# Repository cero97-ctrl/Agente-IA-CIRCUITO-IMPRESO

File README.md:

# Agente IA de Fabricación Digital.

## Estado del Proyecto
El proyecto está en desarrollo activo. Las funcionalidades principales de generación de modelos 3D y PCBs son estables. El versionado se gestiona automáticamente mediante el script `git-update.sh`.

## Descripción del Proyecto

Este repositorio aloja un **Agente de IA para Fabricación Digital**, accesible a través de un bot de Telegram. El agente está diseñado para ser un asistente de ingeniería que puede interpretar lenguaje natural e imágenes para generar archivos de diseño y fabricación.

El núcleo del sistema utiliza un LLM para la orquestación y scripts deterministas en un entorno Docker para ejecutar tareas complejas de forma fiable, incluyendo el uso de software CAD/ECAD como **FreeCAD** y **KiCad** en modo headless.

## Capacidades Principales

El agente puede realizar las siguientes tareas a través de comandos de Telegram:

### 📐 Diseño CAD 3D (con FreeCAD)
- **Generación Paramétrica**: Crea modelos 3D (cubos, cilindros, esferas, conos) a partir de descripciones en lenguaje natural (ej. `/freecad un cono de radio 10 y altura 30`).
- **Exportación Multi-formato**: Genera archivos `.stl` (para impresión 3D), `.step` (formato industrial) y un render realista en `.png`.
- **Análisis Físico**: Calcula y reporta el volumen y la masa estimada (PLA) del objeto generado.

### ⚡ Diseño Electrónico (con KiCad)
- **Interpretación de Dibujos**: Analiza una foto de un circuito dibujado a mano y genera una netlist estructurada en formato JSON.
- **Generación de Esquemáticos**: Crea un archivo de esquemático (`.kicad_sch`) a partir de la netlist interpretada.
- **Placement de PCB**: Genera un archivo de placa (`.kicad_pcb`) con componentes ubicados de forma óptima para enrutado externo.
- **Exportación Specctra DSN**: Genera archivos `.dsn` compatibles con enrutadores de IA como DeepPCB.
- **Paquetes de Fabricación**: Crea un archivo `.zip` con todos los archivos Gerber y de taladrado (Drill), listo para enviar a fabricantes como JLCPCB o PCBWay.

### ⚙️ Fabricación CNC
- **Generación de G-Code**: Convierte imágenes en blanco y negro a G-Code (`.nc`) para fresado.
- **Comunicación con Máquina**: Incluye un script para enviar G-Code a máquinas CNC que usan el firmware GRBL.

Para una lista completa de comandos y sus descripciones, consulta la Referencia de Comandos.

## Instalación y Puesta en Marcha

El sistema está diseñado para ejecutarse en un entorno contenerizado para máxima portabilidad.

### 1. Requisitos Previos
- **Docker**: Para ejecutar el sandbox que contiene FreeCAD, KiCad y todas las dependencias.
- **Python 3.10+**: Para ejecutar la lógica del agente.

### 2. Clonar el Repositorio
```bash
git clone https://github.com/cero-etage/Agente-IA-CIRCUITO-IMPRESO.git
cd Agente-IA-CIRCUITO-IMPRESO
```

### 3. Configurar el Entorno
Crea un archivo `.env` en la raíz del proyecto y añade tus claves de API. Puedes usar el siguiente ejemplo como plantilla:
```env
TELEGRAM_BOT_TOKEN="tu_token_de_telegram"
TELEGRAM_CHAT_ID="tu_chat_id"

# Elige al menos un proveedor de LLM
GROQ_API_KEY="tu_api_key_de_groq"
GOOGLE_API_KEY="tu_api_key_de_google"
OPENAI_API_KEY="tu_api_key_de_openai"
ANTHROPIC_API_KEY="tu_api_key_de_anthropic"
```

### 4. Construir el Sandbox de Docker
Este comando crea la imagen de Docker con todas las herramientas CAD/ECAD necesarias. Puede tardar un poco la primera vez.
```bash
python execution/build_sandbox.py
```

### 5. Instalar Dependencias de Python
```bash
pip install -r requirements.txt
```

### 6. Ejecutar el Agente
Una vez configurado, inicia el bot que escuchará los comandos de Telegram.
```bash
python execution/listen_telegram.py
```

### 🚀 Optimización para Recursos Limitados (ZRAM)
Para ejecutar modelos locales como `gemma:2b` de forma eficiente sin agotar la RAM física, el sistema utiliza **ZRAM** (Memoria Intercambio Comprimida). 

**Configuración Recomendada:**
- **Algoritmo**: `zstd` (mejor ratio de compresión).
- **Tamaño**: 50% - 60% de la RAM física.
- **Swappiness**: `150` (indica al kernel que prefiera comprimir memoria inactiva antes de usar el disco).

Esta configuración permite que el sistema maneje ráfagas de carga de hasta 2x la RAM física disponible sin congelamientos, ideal para entornos de desarrollo en PC con 4GB u 8GB de RAM.

### 🏎️ Escalabilidad: Aceleración por GPU (NVIDIA)
El agente está preparado para escalar a hardware con GPU. Para activar la aceleración CUDA en Ollama:
1. Instalar drivers de NVIDIA y `nvidia-container-toolkit`.
2. El orquestador detectará automáticamente la GPU mediante `nvidia-smi`.
3. Los modelos como `gemma2:9b` o `llama3` podrán ejecutarse con latencia casi nula, liberando la CPU y la ZRAM para tareas de diseño pesado en KiCad/FreeCAD.

## Documentación Detallada

Para una inmersión profunda en el proceso de diseño de PCBs con CNC, las herramientas y los scripts de Python involucrados, consulta el documento principal que originó esta investigación:

Documentación del Flujo de Trabajo CNC con Python

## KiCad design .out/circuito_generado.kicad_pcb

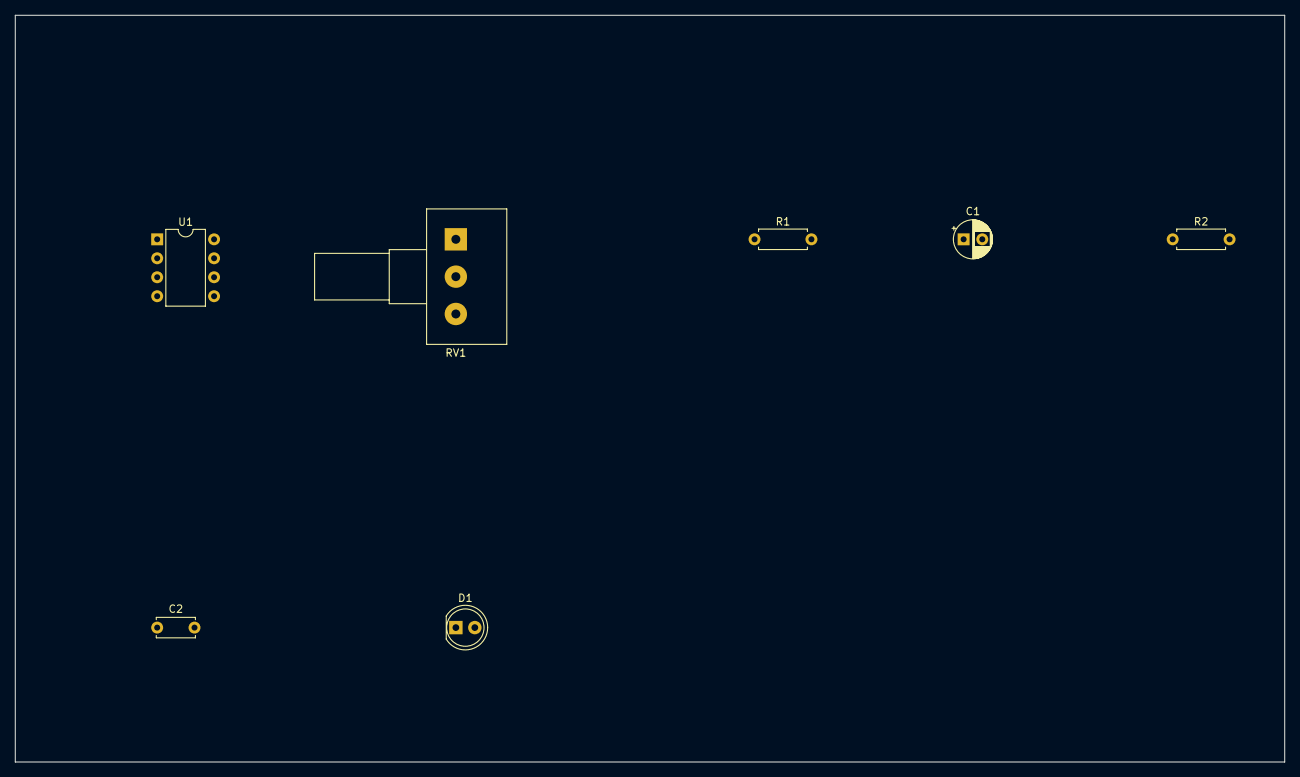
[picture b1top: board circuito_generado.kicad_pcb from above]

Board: 2 copper layers, 170.0 x 100.0 mm, 7 parts (0 on the bottom side), 7 nets, no tracks yet.

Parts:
C1: CP_Radial_D5.0mm_P2.50mm
C2: C_Disc_D5.0mm_W2.5mm_P5.00mm
D1: LED_D5.0mm
R1, R2: R_Axial_DIN0207_L6.3mm_D2.5mm_P7.62mm_Horizontal
RV1: Potentiometer_Alps_RK163_Single_Horizontal
U1: DIP-8_W7.62mm

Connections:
GND: C1.1, C2.2, R2.2, U1.1
NET_CONTROL_VOLTAGE: C2.1, U1.5
NET_LED_CURRENT_LIMIT: D1.1, R2.1
NET_LED_OUT: D1.2, U1.3
NET_RA_DISCHARGE: R1.1, RV1.2, U1.7
NET_RB_TRIGGER_THRESHOLD: C1.2, R1.2, U1.2, U1.6
VCC_9V: RV1.1, U1.4, U1.8

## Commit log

2026-02-23 Initial commit for Agente-IA-CNC
2026-02-24 WIP: guardar cambios antes de pull
2026-02-26 Initial commit for Agente-IA-CIRCUITO-IMPRESO
2026-02-28 Version v1.0.0
2026-02-28 Version v1.0.1
2026-03-01 Version v1.0.2
2026-03-01 Version v1.0.3
2026-03-01 Version v1.0.4
2026-03-04 Version v1.0.5
2026-03-04 Version v1.0.6
2026-03-07 Version v1.0.7
2026-03-07 Version v1.0.8
2026-03-07 Version v1.0.9
2026-03-10 Version v1.0.10
2026-03-16 Version v1.0.11
2026-03-24 Version v1.0.12
2026-03-27 Version v1.0.13
2026-03-27 Version v1.0.14
2026-03-27 Version v1.0.15
2026-03-28 Version v1.0.16
2026-03-29 Version v1.0.17
2026-03-29 Version v1.0.18
2026-03-29 Version v1.0.19
2026-03-30 Version v1.0.20
2026-04-01 Version v1.0.21
2026-04-05 Version v1.0.22
2026-04-09 Version v1.0.23
2026-04-09 Version v1.0.24
2026-04-10 Version v1.0.25
2026-04-10 Version v1.0.26
2026-04-10 Version v1.0.27
2026-04-10 Version v1.0.28
2026-06-23 Version v1.0.29
